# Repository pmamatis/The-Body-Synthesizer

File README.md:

Welcome to our lovely project. THE BODY-SYNTHESIZER. This is an educational project, which has been the topic of a course in digital signal processing and electronics at the Technical University Berlin, and is for non-commercial use only. The main goal of the project was to realize a digital audio-synthesizer, which can be controlled by various analog sensors. In case you wanna have a quick overview about the functionality, you can access the following YouTube-link: https://www.youtube.com/watch?v=VzIIO2eS0HQ&t=1586s

By: <br>
Maximillian Lehmer <br> Marc Bielen <br> Paul Mamatis

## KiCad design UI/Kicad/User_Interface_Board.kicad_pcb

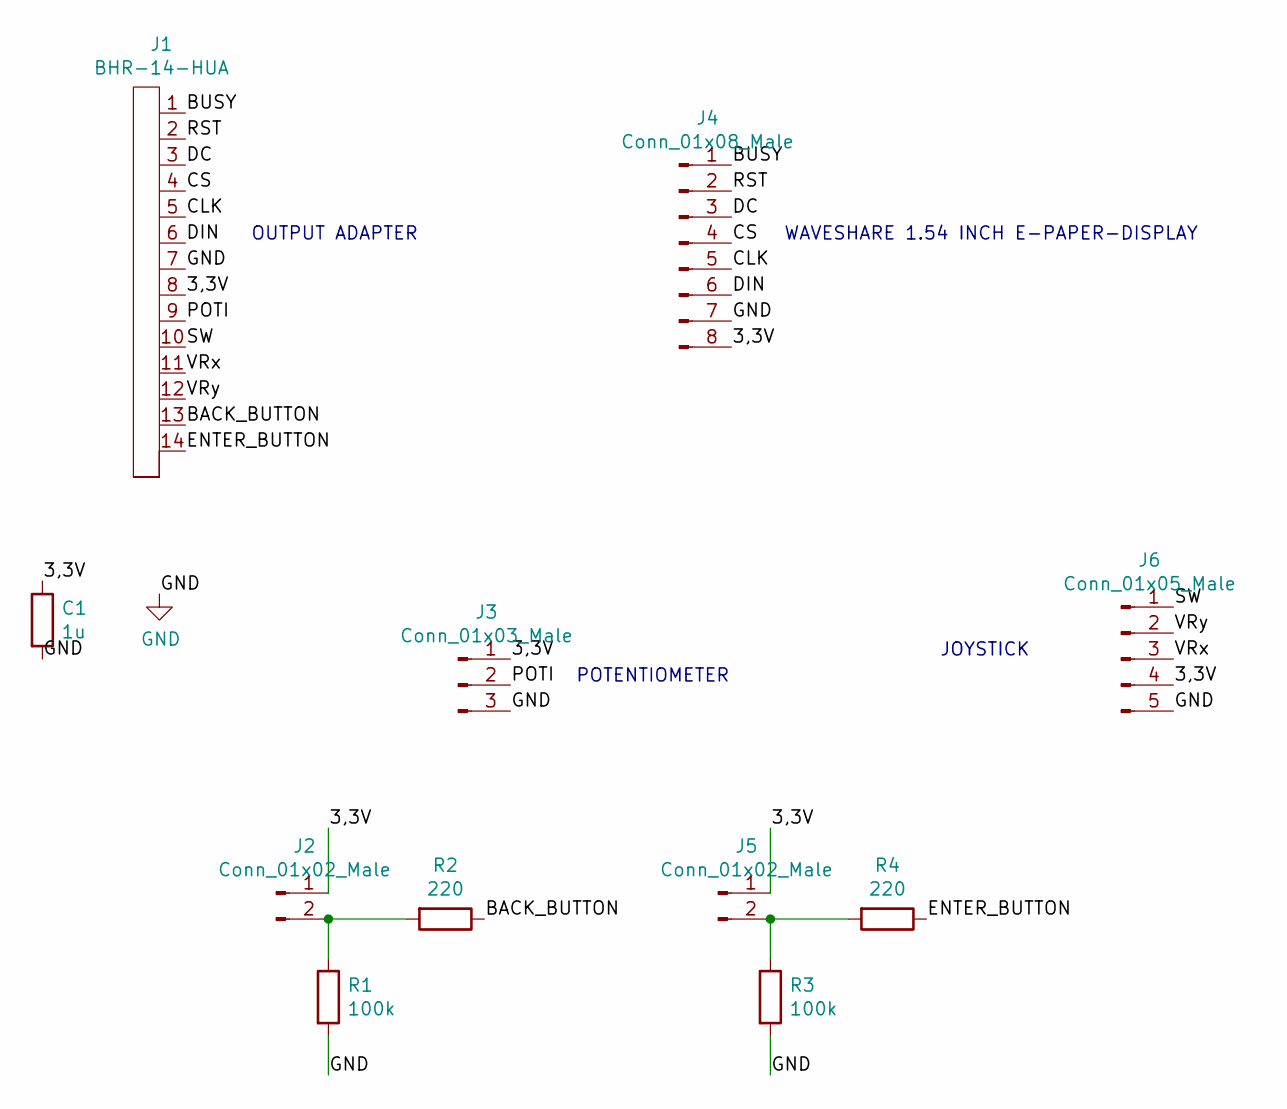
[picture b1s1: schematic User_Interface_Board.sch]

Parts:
C1: 1u; C_0805_2012Metric
J1: BHR-14-HUA
J2, J5: Conn_01x02_Male; PinHeader_1x02_P2.54mm_Vertical
J3: Conn_01x03_Male; PinHeader_1x03_P2.54mm_Vertical
J4: Conn_01x08_Male; PinSocket_1x08_P2.54mm_Vertical
J6: Conn_01x05_Male; PinSocket_1x05_P2.54mm_Vertical
R1, R3: 100k; R_0805_2012Metric
R2, R4: 220; R_0805_2012Metric

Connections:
/3,3V: C1.1, J1.8, J2.1, J3.1, J4.8, J5.1, J6.4
/BACK_BUTTON: J1.13, R2.1
/BUSY: J1.1, J4.1
/CLK: J1.5, J4.5
/CS: J1.4, J4.4
/DC: J1.3, J4.3
/DIN: J1.6, J4.6
/ENTER_BUTTON: J1.14, R4.1
/POTI: J1.9, J3.2
/RST: J1.2, J4.2
/SW: J1.10, J6.1
/VRx: J1.11, J6.3
/VRy: J1.12, J6.2
GND: C1.2, J1.7, J3.3, J4.7, J6.5, R1.2, R3.2
unnamed: J2.2, R1.1, R2.2
unnamed: J5.2, R3.1, R4.2

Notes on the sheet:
WAVESHARE 1.54 INCH E-PAPER-DISPLAY
JOYSTICK
POTENTIOMETER
OUTPUT ADAPTER

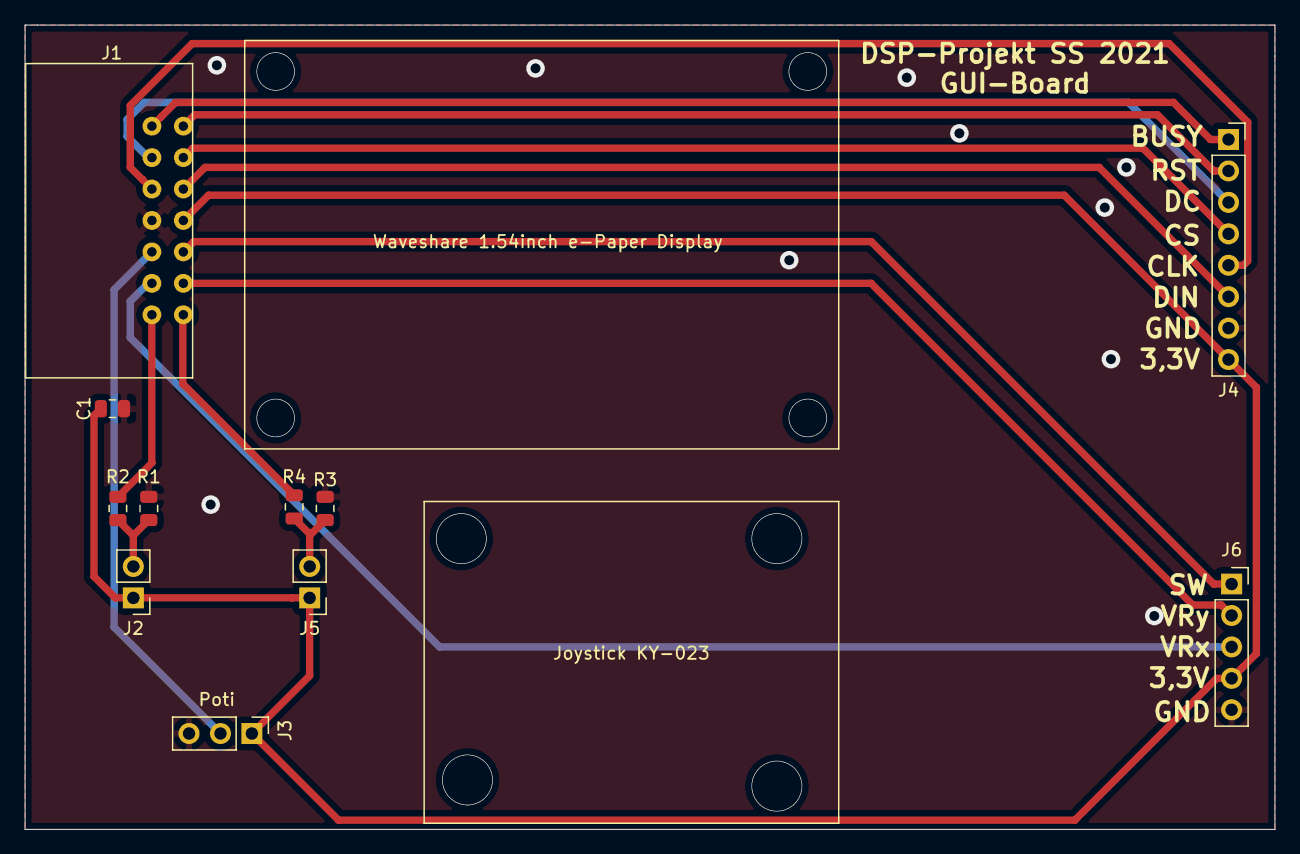
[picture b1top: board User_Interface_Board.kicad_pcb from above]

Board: 2 copper layers, 101.0 x 65.0 mm, 11 parts (0 on the bottom side), 16 nets.

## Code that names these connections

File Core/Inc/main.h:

/* USER CODE BEGIN Header */
/**
 ******************************************************************************
 * @file           : main.h
 * @brief          : Header for main.c file.
 *                   This file contains the common defines of the application.
 ******************************************************************************
 * @attention
 *
 * <h2><center>&copy; Copyright (c) 2019 STMicroelectronics.
 * All rights reserved.</center></h2>
 *
 * This software component is licensed by ST under BSD 3-Clause license,
 * the "License"; You may not use this file except in compliance with the
 * License. You may obtain a copy of the License at:
 *                        opensource.org/licenses/BSD-3-Clause
 *
 ******************************************************************************
 */
/* USER CODE END Header */

/* Define to prevent recursive inclusion -------------------------------------*/
#ifndef __MAIN_H
#define __MAIN_H

#ifdef __cplusplus
extern "C" {
#endif

/* Includes ------------------------------------------------------------------*/
#include "stm32f7xx_hal.h"

/* Private includes ----------------------------------------------------------*/
/* USER CODE BEGIN Includes */
#include <stdbool.h>

// for signal synthesis
#include "signal_synthesis.h"
#include "music_notes.h"
#include "sinLUT.h"
#include "effects.h"

// for filters
#include "filters.h"
#include "arm_math.h"
#include "math_helper.h"
#include "adsr.h"
#include "keyboard.h"
#include "tremolo.h"
#include "wahwah.h"
#include "distortion.h"
#include "emg.h"
#include "drum_computer.h"
#include "display.h"
#include "input_interfaces.h"
#include "SPI_Connection.h"	// Gyroscope SPI

/* USER CODE END Includes */

/* Exported types ------------------------------------------------------------*/
/* USER CODE BEGIN ET */

/* USER CODE END ET */

/* Exported constants --------------------------------------------------------*/
/* USER CODE BEGIN EC */

/* USER CODE END EC */

/* Exported macro ------------------------------------------------------------*/
/* USER CODE BEGIN EM */

/* USER CODE END EM */

/* Exported functions prototypes ---------------------------------------------*/
void Error_Handler(void);

/* USER CODE BEGIN EFP */

/* USER CODE END EFP */

/* Private defines -----------------------------------------------------------*/
#define F4_SPI_CLK_Pin GPIO_PIN_2
#define F4_SPI_CLK_GPIO_Port GPIOE
#define F4_SPI_MISO_Pin GPIO_PIN_5
#define F4_SPI_MISO_GPIO_Port GPIOE
#define F4_SPI_MOSI_Pin GPIO_PIN_6
#define F4_SPI_MOSI_GPIO_Port GPIOE
#define ENTER_USER_Pin GPIO_PIN_13
#define ENTER_USER_GPIO_Port GPIOC
#define ENTER_USER_EXTI_IRQn EXTI15_10_IRQn
#define GYRO_I2C_SDA_Pin GPIO_PIN_0
#define GYRO_I2C_SDA_GPIO_Port GPIOF
#define GYRO_I2C_SCL_Pin GPIO_PIN_1
#define GYRO_I2C_SCL_GPIO_Port GPIOF
#define ADC_EMG_DC_Pin GPIO_PIN_6
#define ADC_EMG_DC_GPIO_Port GPIOF
#define ADC_EMG_AC_Pin GPIO_PIN_7
#define ADC_EMG_AC_GPIO_Port GPIOF
#define SD_CS_Pin GPIO_PIN_10
#define SD_CS_GPIO_Port GPIOF
#define Poti_Pin GPIO_PIN_0
#define Poti_GPIO_Port GPIOC
#define KEYBOARD_ADC_Pin GPIO_PIN_2
#define KEYBOARD_ADC_GPIO_Port GPIOC
#define DISP_DC_Pin GPIO_PIN_0
#define DISP_DC_GPIO_Port GPIOA
#define VRx_Pin GPIO_PIN_6
#define VRx_GPIO_Port GPIOA
#define VRy_Pin GPIO_PIN_0
#define VRy_GPIO_Port GPIOB
#define DISP_BUSY_Pin GPIO_PIN_1
#define DISP_BUSY_GPIO_Port GPIOB
#define SD_DI_MOSI_Pin GPIO_PIN_2
#define SD_DI_MOSI_GPIO_Port GPIOB
#define DISP_RST_Pin GPIO_PIN_12
#define DISP_RST_GPIO_Port GPIOF
#define SW_Pin GPIO_PIN_0
#define SW_GPIO_Port GPIOG
#define ENTER_Pin GPIO_PIN_8
#define ENTER_GPIO_Port GPIOE
#define ENTER_EXTI_IRQn EXTI9_5_IRQn
#define Red_User_LED_Pin GPIO_PIN_14
#define Red_User_LED_GPIO_Port GPIOB
#define DISP_CS_Pin GPIO_PIN_8
#define DISP_CS_GPIO_Port GPIOC
#define BACK_Pin GPIO_PIN_9
#define BACK_GPIO_Port GPIOC
#define BACK_EXTI_IRQn EXTI9_5_IRQn
#define SD_CLK_Pin GPIO_PIN_10
#define SD_CLK_GPIO_Port GPIOC
#define SD_DO_MISO_Pin GPIO_PIN_11
#define SD_DO_MISO_GPIO_Port GPIOC
#define DISP_CLK_Pin GPIO_PIN_3
#define DISP_CLK_GPIO_Port GPIOB
#define DISP_DIN_Pin GPIO_PIN_5
#define DISP_DIN_GPIO_Port GPIOB
#define Blue_User_LED_Pin GPIO_PIN_7
#define Blue_User_LED_GPIO_Port GPIOB
/* USER CODE BEGIN Private defines */

/**@brief number of support points for a single period*/
#define SUPPORT_POINTS 20

/**@brief output array size */
#define BLOCKSIZE 480 // Latenz = 20ms @ 24kHz S

/** @brief DAC output array*/

/** DAC output array. Before the content of this array is given to the DAC, all calculations are made on this array too  */
float calculate_vector1[BLOCKSIZE];
float calculate_vector2[BLOCKSIZE];

/** Array for the LFO(low frequency oscillator)*/
float effect_LFO[BLOCKSIZE/2];

/** @brief enum for DMA Output buffer position */
enum outputBuffer_position_enum{
	HALF_BLOCK = 0,
	FULL_BLOCK
};

/* USER CODE END Private defines */

#ifdef __cplusplus
}
#endif

#endif /* __MAIN_H */

/************************ (C) COPYRIGHT STMicroelectronics *****END OF FILE****/

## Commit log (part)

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2020-06-24 all_sines_LUT.m added
2020-06-24 cosmetics
2020-06-24 1.4 in progress
2020-06-24 dlmwrite
2020-06-30 LUT code writer 1.0
2020-06-30 sinLLUT
2020-07-02 verbessert
    LFO geht nicht
2020-07-07 BLOCKSIZE = 24k, wegen RAM speicher
    LUT und LFO im Flash gespeichert
2020-07-07 LFO calculate verbessert
    LUT und LFo in Flash schreiben hinzugefügt
2020-07-08 LFO Periode/4
2020-07-08 Samplerate = 96k
2020-07-08 Picture added
2020-07-30 Signal Syntrhesis 1.4 works first atempt, no bugs found but also not searched
2020-08-04 Signalsyntheses, möglicherweise fertig?!
2020-08-06 dynamische Voice Lautstärke
2020-08-12 changed LFO precision from 2 to 5
2020-08-12 LFO ready to use
2020-08-12 filters merged with new signal synthesis, LP test successful
2020-09-28 less RAM usage
    calculate_vector isnow directly given to the DAC, without having the output_vector
2020-09-30 Tremolo works, but still have to clean up!
2020-09-30 Tremolo is implemented!
2021-01-21 organized the code for the distortion-effect
2021-03-04 Add new directory by wiselom
2021-04-25 EMG board updates
2021-04-25 BSB.graphml added
2021-04-25 Lowpass filter working still! Next up: try band/highpass
2021-05-02 added Together Branch, merged tremolo and filters
2021-05-07 debug session
2021-05-07 debug session gelöst
2021-05-07 nichts hat sich veränder "nochmal pushen"
2021-05-14 merging begins
2021-05-14 Master -Branch First Commit
    This Branch must contain only working states of the Software. Use this Branch to develop and then merge back if everything is functional
2021-05-16 Parallel processing implemented: works for 1 band already, next up: Test all bands at the same time
2021-05-16 All bands tested at the same time with several test tones, worked! Next up: have a look to amplitude levels (e.g. testing filters with white noise)
2021-05-19 define aquidistance and atan_LUT_y in distortion-files instead of main-files
2021-05-21 added soft clipping based on exponential function;
    added CMSIS-DSP and CMSIS-Core-Library
2021-05-21 EQ Bandpass debugged, Band 1 & 2 working properly - Next up: Test Band 3 - 5
2021-05-23 Individual Bandpass filters implemented, center frequencies have to be specified
2021-05-23 started with the new structure, which should be implemented
2021-05-25 now it is possible to turn Voice1 Off and On again
2021-05-26 Switching between Voices, ADSR, EQ, Distortion and Tremolo possible
2021-05-27 Code angepasst
2021-06-01 Keyboard slightly edited (2 drills) for manufacturing
2021-06-01 ADC reads AC (in12) and DC (in13) channel of emg
2021-06-02 All types of filter implemented, next up: test new ones with poti (change cutoff, Q, Gain)
2021-06-02 Warnings solved, now Signal_Syntheis Errors occured >> Will be fixed by Paul and Marc
2021-06-02 Keyboard panelized
2021-06-02 emg adc ready to use
2021-06-06 ADC1 Channel 13 read in for poti value while signal synthesis as well as printing via uart is working
2021-06-06 Debugging necessary
2021-06-07 Tremolo does not work in combination with display; permanent calculation of LFO could be the problem
2021-06-08 Voice, Distortion and Tremolo work together; had to remove effects_process and put function calls into signal_synthesis
2021-06-11 HS / LS tested successfully with changing Gain & Cutoff in Filters_Reinit() - next up: PEQ
2021-06-11 PEQ Att. Problem solved by introducing Notch filter >> Complete EQ works now!
2021-06-13 Mainboard created
2021-06-13 pinbelegung für display geändert (SPI)
2021-06-18 changed CLK and MOSI from SPI6 to SPI1 for the display
2021-06-18 changed Button_Back and DISP_CS pins
2021-06-21 Pinout test done, SD card works in this setup!
2021-06-21 update rotation of the display
2021-06-22 integrated keyboardmode on/off, bu adsr reacts too slow. processing has to be done at different place
2021-06-22 Auf dem stand von Keyboard-Branch, ADSR weißt dennoch Fehler auf
2021-06-24 Optimized for speed, keyboard can be played now
2021-06-25 ADSR works in combination with the display! Now its possible to switch between keyboard- and synthesizemode and play with the parameters
2021-06-27 soft clipping added, but amplitude does change when gain is increased
2021-06-28 Bemaßung hinzugefügt
2021-07-10 Mainboard updated II
2021-07-15 Mainboard updated IV
2021-07-18 Mainboard updated VI (ready2route)
2021-07-18 Mainboard updated VIII: routed completely, only need to check SD Card size
2021-07-20 Production data for ordering Mainboard, Keys, UI and EQ at JLCPCB
2021-07-21 Production data changed
2021-07-22 Display-Update stört Signale nicht mehr so stark, da nun seltener geupdated wird
2021-08-12 Namen zurechtgerückt
2021-08-12 Display structure changed
2021-08-13 new basic structure implemented
2021-08-13 EQ BOM updated
2021-08-15 BOM updated
2021-08-15 added input_interfaces files
2021-08-19 deleted HAL_ADC_Start_DMA(&hadc1, &Display.ADC1input, 1); in main.c file
2021-08-23 added Interface Controll
2021-08-23 p_Equalizer_Settings implemented and now ready to merge with p_Equalizer_Overview
2021-08-23 p_Equalizer_overview and p_Equalizer_Settings combined
2021-08-24 cleaned up code
2021-08-24 Voices page is working
2021-08-25 Peak detection implemented, not properly working with LED
2021-08-31 EKG Recognition working!!!
2021-09-02 Added pictures for EMG and Mainboard for final report
2021-09-03 display structure is running correctly, but filter page is buggy, when filter is turned on
2021-09-03 drum computer works! now lookup tables have to be read in via sd card
2021-09-03 fixed some display-bugs and dummy structure has to be implemented
2021-09-04 Single Output already possible
2021-09-04 Drumsaples added, reading from SD card works, only need to find a solution for puting LUTs into FLASH and not RAM
2021-09-05 Tried to stream samplewise from SD Card, implicit Bug because of missing header?
2021-09-09 Drum_Computer now working with 4 Samples at a time, loading them from SD card into RAM. Drumsamples are sampled down by 4
2021-09-09 Poti & Filters included to have a lowshelf filter on drums with settable cutoff
2021-09-10 Test
2021-09-10 invert/toggle DrumMatrix entrys in GPIO external interrupt Callback; next filled rectangle should be set/reset
2021-09-10 LFO uncommented
2021-09-10 Drums working together with NewSignal and partly with Filtercutoff reinit. SR: 48kHz, sinLUTs and wavLUTs adapted via matlab scripts. Next up: Trying bigger blocksizes or even lower SR?
2021-09-10 48 kHz change
2021-09-10 9 voices + 4 drums + eq + tremolo + distortion
2021-09-10 Fettes Noise (nun normalized) + Filter + Drums
2021-09-10 24kHz change - drums working nicely
2021-09-11 New drumkit plus updated matlab file, need to go on there
2021-09-11 Rock loud drumkit added
2021-09-11 Tremolo cleaned, WahWah already created, need to finish it
2021-09-11 cosmetics, LFO_FMIN adapted to new low Hz LUTs
2021-09-11 Lowest frequency bug and wrong number of frequencies fixed
2021-09-11 naice ambient lfo wah with poti for future live set
2021-09-11 Noise tested with WahWah, reinitialisation update rate decreased due to high calculation intensity of noise and filter reinit
2021-09-12 drum matrix pattern is displayed whenever you switch into the p_Drumcomputer_Settings function
2021-09-13 Sequencer framwork working for one note to be played together with adsr and drums, keyboard flag changed, next up: add more possible notes
2021-09-13 Changed ADSR if bounderies as well as drumcomputer resetting drum_index to 0 but click bug still existing
2021-09-16 drum computer and sequencer now ready to merge into the display
2021-09-17 filterd with GYro working
2021-09-19 Backup Gyroskop_Paul
2021-09-23 drummachine merge, callback main.c still to do (Button), .ioc check
2021-09-24 added GPIO callback to main function
2021-09-25 added volume and presets function -> fuckup, when keyboard is played at the same time as drumcomputer/sequencer. Problem with IDs?
2021-09-26 mofified delete_effects
2021-09-26 wah wah and autowahwah implemented -> settings have to be implemented in the display
2021-09-28 keyboard is making problems
2021-09-30 successful detection of UP&DOWN and RIGHT&LEFT movements
2021-10-01 keyboard can be played with 3 simultaneous notes, adsr tail deleted by increasing keyboard SR, SetTimerSettings has to be TIM case sensitive, keyboard is cutting signal when played too fast
2021-10-02 Readded sound samples
2021-10-02 keyboard is completed
2021-10-02 all drum samples adjusted to start from sample 1 without delay
2021-10-02 fuckup, when preset is entered: limiting function still wrong
2021-10-03 tremolo- and wahwah- lfo rate bug fixed
2021-10-06 pushen an pauls b-day
2021-10-06 emg in process
2021-10-07 extended preset function
2021-10-13 "plöp"-sound in voices reduced by putting it into signal synthesis and II_Display_Voices
2021-10-13 fixed some display bug in wahwah, settings, but mid freq still plotted in overview page when autowahwah is used
2021-10-15 deleteSignal neu machen, plop am anfang über init gelöst?
2021-10-16 merged Paul and Elom <3
2021-10-17 improved tremolo rate change, but it is still making problems
2021-10-20 changed LFO_SingleValueProcess
2021-10-20 tried to change tremolo depth on each max. of a sine wave, but still some bugs in amp jumping
2021-10-22 tremolo and wahwah work without any amplitude fuckups;
    poti averaged to reduce influence of noise;
    display cosmetics with poti_moved etc.
2021-10-24 button interrupt preemtpion priority increased (from 1 to 0);
    currently loaded drumkit shown above name of samples
2021-10-27 noise generator implemented
2021-10-28 tremolo rate controllable via gyro/accelerometer
2021-11-04 all initialized parameters are set in the display;
    drumkit can be changed without a fuckup;
    button changed for drumkit from left to right button;
    BPM changes only after fourfour, but display is not updated immediately
2021-11-05 max. amplitude (volume) limited to 0.3
2021-11-05 Elom added, SR problem needs to be fixed
2021-11-11 drumfilter works, but the page has to be changed from the equalizer page to the drumcomputer page
2021-11-11 EMG page eingerichtet, aber die maximalen werte müssen noch durch probieren angepasst werden
2021-11-12 Preset 2 added
2021-11-12 drumfilter implemented
2021-11-17 distortion ready and merged
2021-11-19 currently implementing presets
2021-11-20 tremolo and wah wah-lfo frequency rate bug fixed
2021-11-21 Revert "changed ioc settings: timer 5 and timer 6 to timer 1 & irq priorities"
    This reverts commit 021bad5e3134a7439191309bfdfd77357e1c5b76.
    changeg display spi baud rate, extended wahwah_sources size, volume adjusted to lower values for testing, usart2 (former sd card test usart) deleted
2021-11-21 3 presets implemented
2021-11-21 ecg heartrate bpm control implemented, but not working yet
2021-11-23 Surprise commit
2021-11-26 ECG and EMG tested and parameters are integrated into the display page
2021-11-27 BPM updated in display while changed by ECG
2021-11-27 major, minor and freestyle scale modes work for Voices and hardcoded for gyro voices yet
2021-12-01 Major, Minor and Freestyle Scale implemented into sequencer - it works
2021-12-01 adjusted filter input interfaces to sweep faster while playing EQ with gyro and Filters_Reinit_Gyro function
2021-12-27 cleaned up code by removing unnecessary variables and comments
2022-01-05 Bereinigter Code um ihn an den Bericht anzuhängen
2022-01-06 header files kommentiert
2022-01-21 all files are commentet
2022-01-31 first Doku Version ready
2022-02-04 doxygen-Doku ergänzt
2022-02-04 kompelierbar
2022-02-07 cosmetics for report
2022-02-17 Drumcomputer / Sequencer graphmls added
2022-02-20 Sch bild
2022-02-20 keyboard brdV2 pic added
2022-02-20 Keyboard pictures added and sch updated
2022-02-22 Doxgen um Matlab erweitert
2022-02-22 Matlab works
2022-02-22 Revert ".gitignore update"
    This reverts commit 651362b3661256f62fe27b7781636f0aba2e56b7.
2022-02-22 Alles wieder im Lot commit :D
2022-02-22 updated Distortion_LUT.m
2022-03-02 DCS BSBs updated
2022-03-06 Filter plots extended
2022-03-29 Some briefs & correctures
2022-03-30 Neu Kompiliert
2022-03-31 Sensor_code update
